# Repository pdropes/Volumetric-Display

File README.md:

# Volumetric-Display, with ESP32 and LED matrix

VOXEL by #dropes

Video: https://youtu.be/vmjfssugH9E

## VOXEL - HARDWARE

- The motor I used the head of a VCR, after opening it, I placed the power transmitter coils inside, the ferrites had to be filed (very carefully) to fit well and then glued them.
- The distance between the coils is very important and must be calibrated in advance, with the help of a power supply with adjustable maximum current. In the receiver, you must connect a low value resistance 2ohms, or a 20W 12V lamp, with a multimeter to monitor the current passing through it.
- Then the emitter must be supplied with 12V, without progressive increases, the supply must be immediate or it will burn out, maximum current of 2A to start.
- The objective is to have the maximum current measured in the receiver, but without saturating the coils, to do this the distance between the coils is slowly reduced, the current rises to a point, then starts to fall, the distance from the coil must be recorded highest measured current.
- It is likely that the source used in these tests will present a current peak when calibrating the distances. You must be very careful not to overheat both the transmitter and the receiver, and you must immediately move the coils away.
- Both must have a heat sink, both on the two boards and on the emitter power transistors.
- The power supply must be at least 50W, with a voltage of 18V to 24V, with a lower voltage the wireless power transmitter will overheat, requiring more current to compensate.
- The IR transmitter and receiver are inside the head through two holes, this head must rotate without touching anything.
- Assembling all the components requires some skills, if you are not able to solder with an oven or heating plate and hot air station, I recommend ordering the PCBs with the components already soldered, joining the two plates will have to be done later.
- The most difficult are the 1024 “0603 LEDs” and the 64 “controller ICs”.
- The PCBs must have the minimum thickness possible, with 0.6mm being a good value, with the LED controller ICs touching them. Their color doesn't matter much, in rotation it becomes unnoticeable.

More calibrations:
- The 1st balance is static, with the boards horizontal and without the tube, weights must be placed, so that no differences are noticed when rotating manually, always horizontally.
- The dynamic balance was achieved by placing a piezo on one of the legs of the box, visualizing the signal amplitude on the oscilloscope, then placing washers at certain points, where the displayed amplitude reduces.
- The tube alignment must also be done, looking for eccentricity and having as little oscillation as possible.
  
These processes can be tedious and time-consuming, be patient.

## VOXEL - SOFTWARE

Project carried out in Arduino IDE v2.2.1
The 1st programming must be via USB, the rest can be via Wi-Fi for the convenience of keeping the tube, this is the best option, the Arduino-ota routine must be configured in advance, with the name and password of the network to be connected, this part must always remain in the code.
Although you chose the ESP32S2, another type of ESP32 should work, it uses the internal RAM for animations, and the optional PSRAM, for pre-calculation of heavier animations.
The USB connection is direct, without the need for a separate IC for this.
Programming the ESP32 must be done with the engine stopped, in all cases.

Programming steps:
- Connect the VOXEL board directly via USB to the PC.
- Open Arduino, in BOARDS MANAGER, find and install “esp32 by Espressif”
- In LIBRARIES MANAGER, find and install “Arduino_ESP32_OTA by Arduino”
- In TOOLS-BOARDS-ESP32-ESP32S2 Dev Module, choose the COM where the VOXEL is connected
- Check the board settings with the attached file “Arduino V2.2.1 config.png”.
- In VOXEL.INO change the name and password of the local network 
- Compile and upload to ESP32.
- After that, all programming does not require a USB connection, on the Arduino IDE, the Wi-Fi port must be visible.
- If you always intend to program via Wi-Fi, the Arduino-ota settings in VOXEL.ino must remain.

New Animation:
- When programming more effects, you must create a blank file in the same folder, extension .h
- Open VOXEL.ino
- Include the new file name in “FX”
- Next, the “FXlast” declaration, must be changed to the last effect number.
- void ISR_IR, which is the int. that detects the complete turn via IR, the procedure to be carried out in this new effect must be included (check the examples already written).
- void ARDUINO_ISR_ATTR, this is a timer that is run 100 times per turn, the reference of the new effect must also be included, or copy 3 lines from another, so that it can be clearly displayed.
- Shared.h file shares variables between VOXEL.ino and effect.h, or use static variables to avoid conflicts.

## WARNING !
The use of acrylic tube is NECESSARY in this assembly!
It keeps the boards in place at the top, prevents air friction, and ensures GREATER SAFETY to the touch.
Its absence can cause PHYSICAL OR VISION DAMAGE, the rotation speed corresponds to between 25 and 42 km/h!

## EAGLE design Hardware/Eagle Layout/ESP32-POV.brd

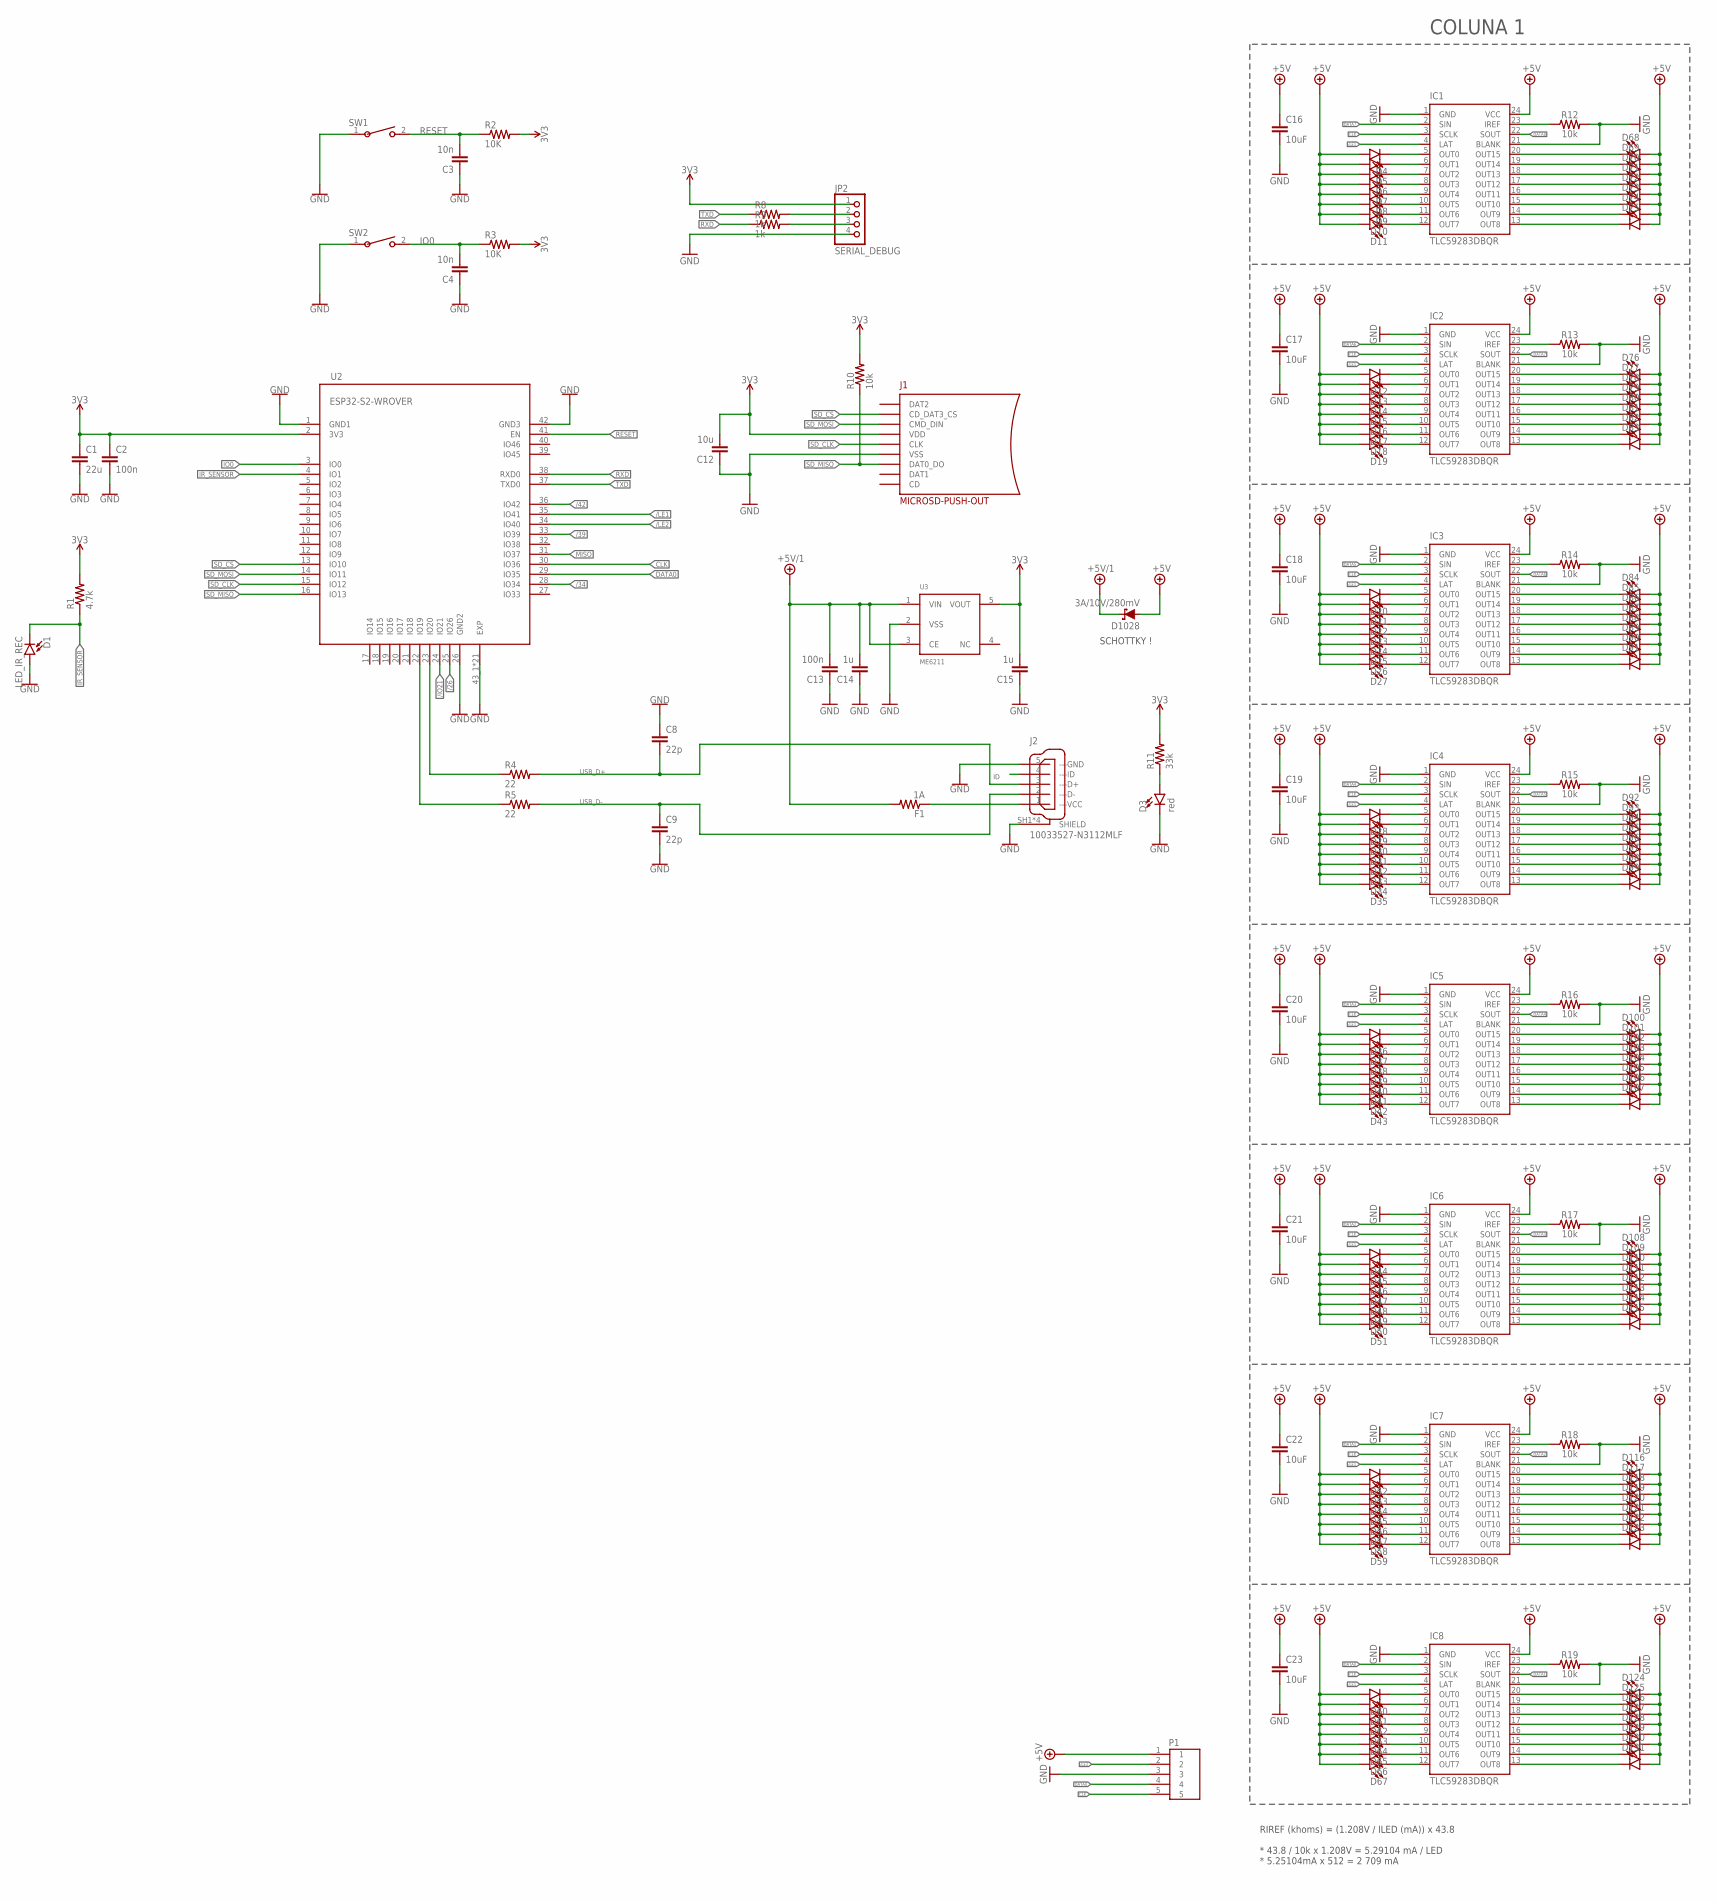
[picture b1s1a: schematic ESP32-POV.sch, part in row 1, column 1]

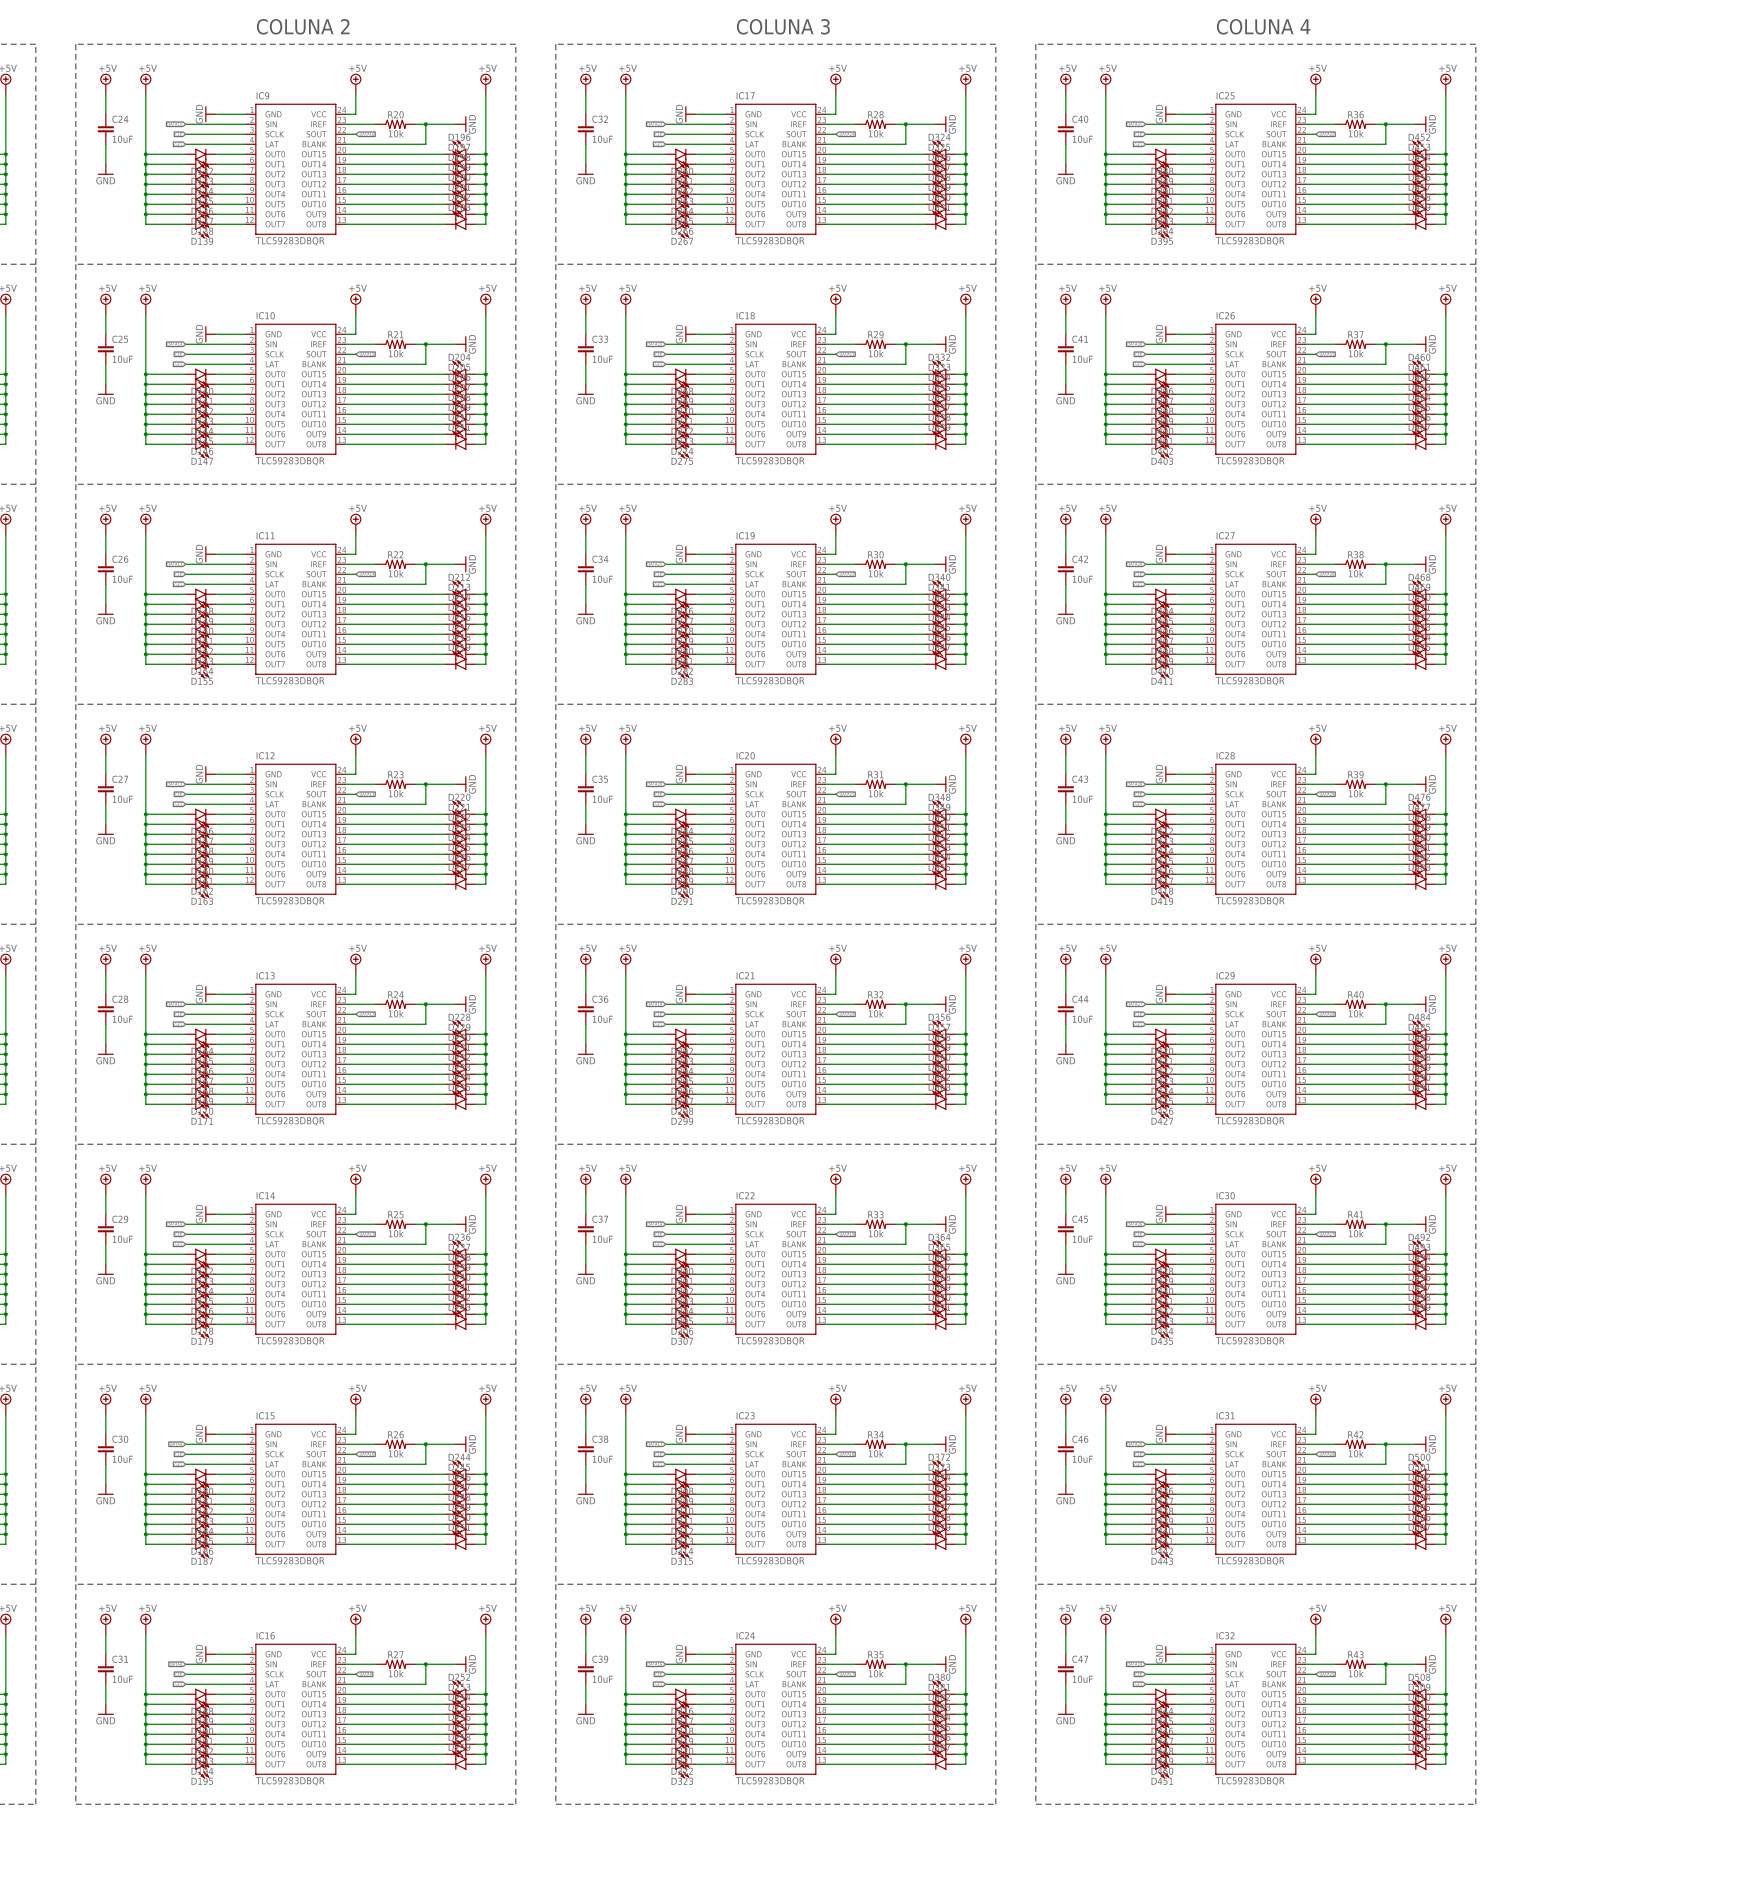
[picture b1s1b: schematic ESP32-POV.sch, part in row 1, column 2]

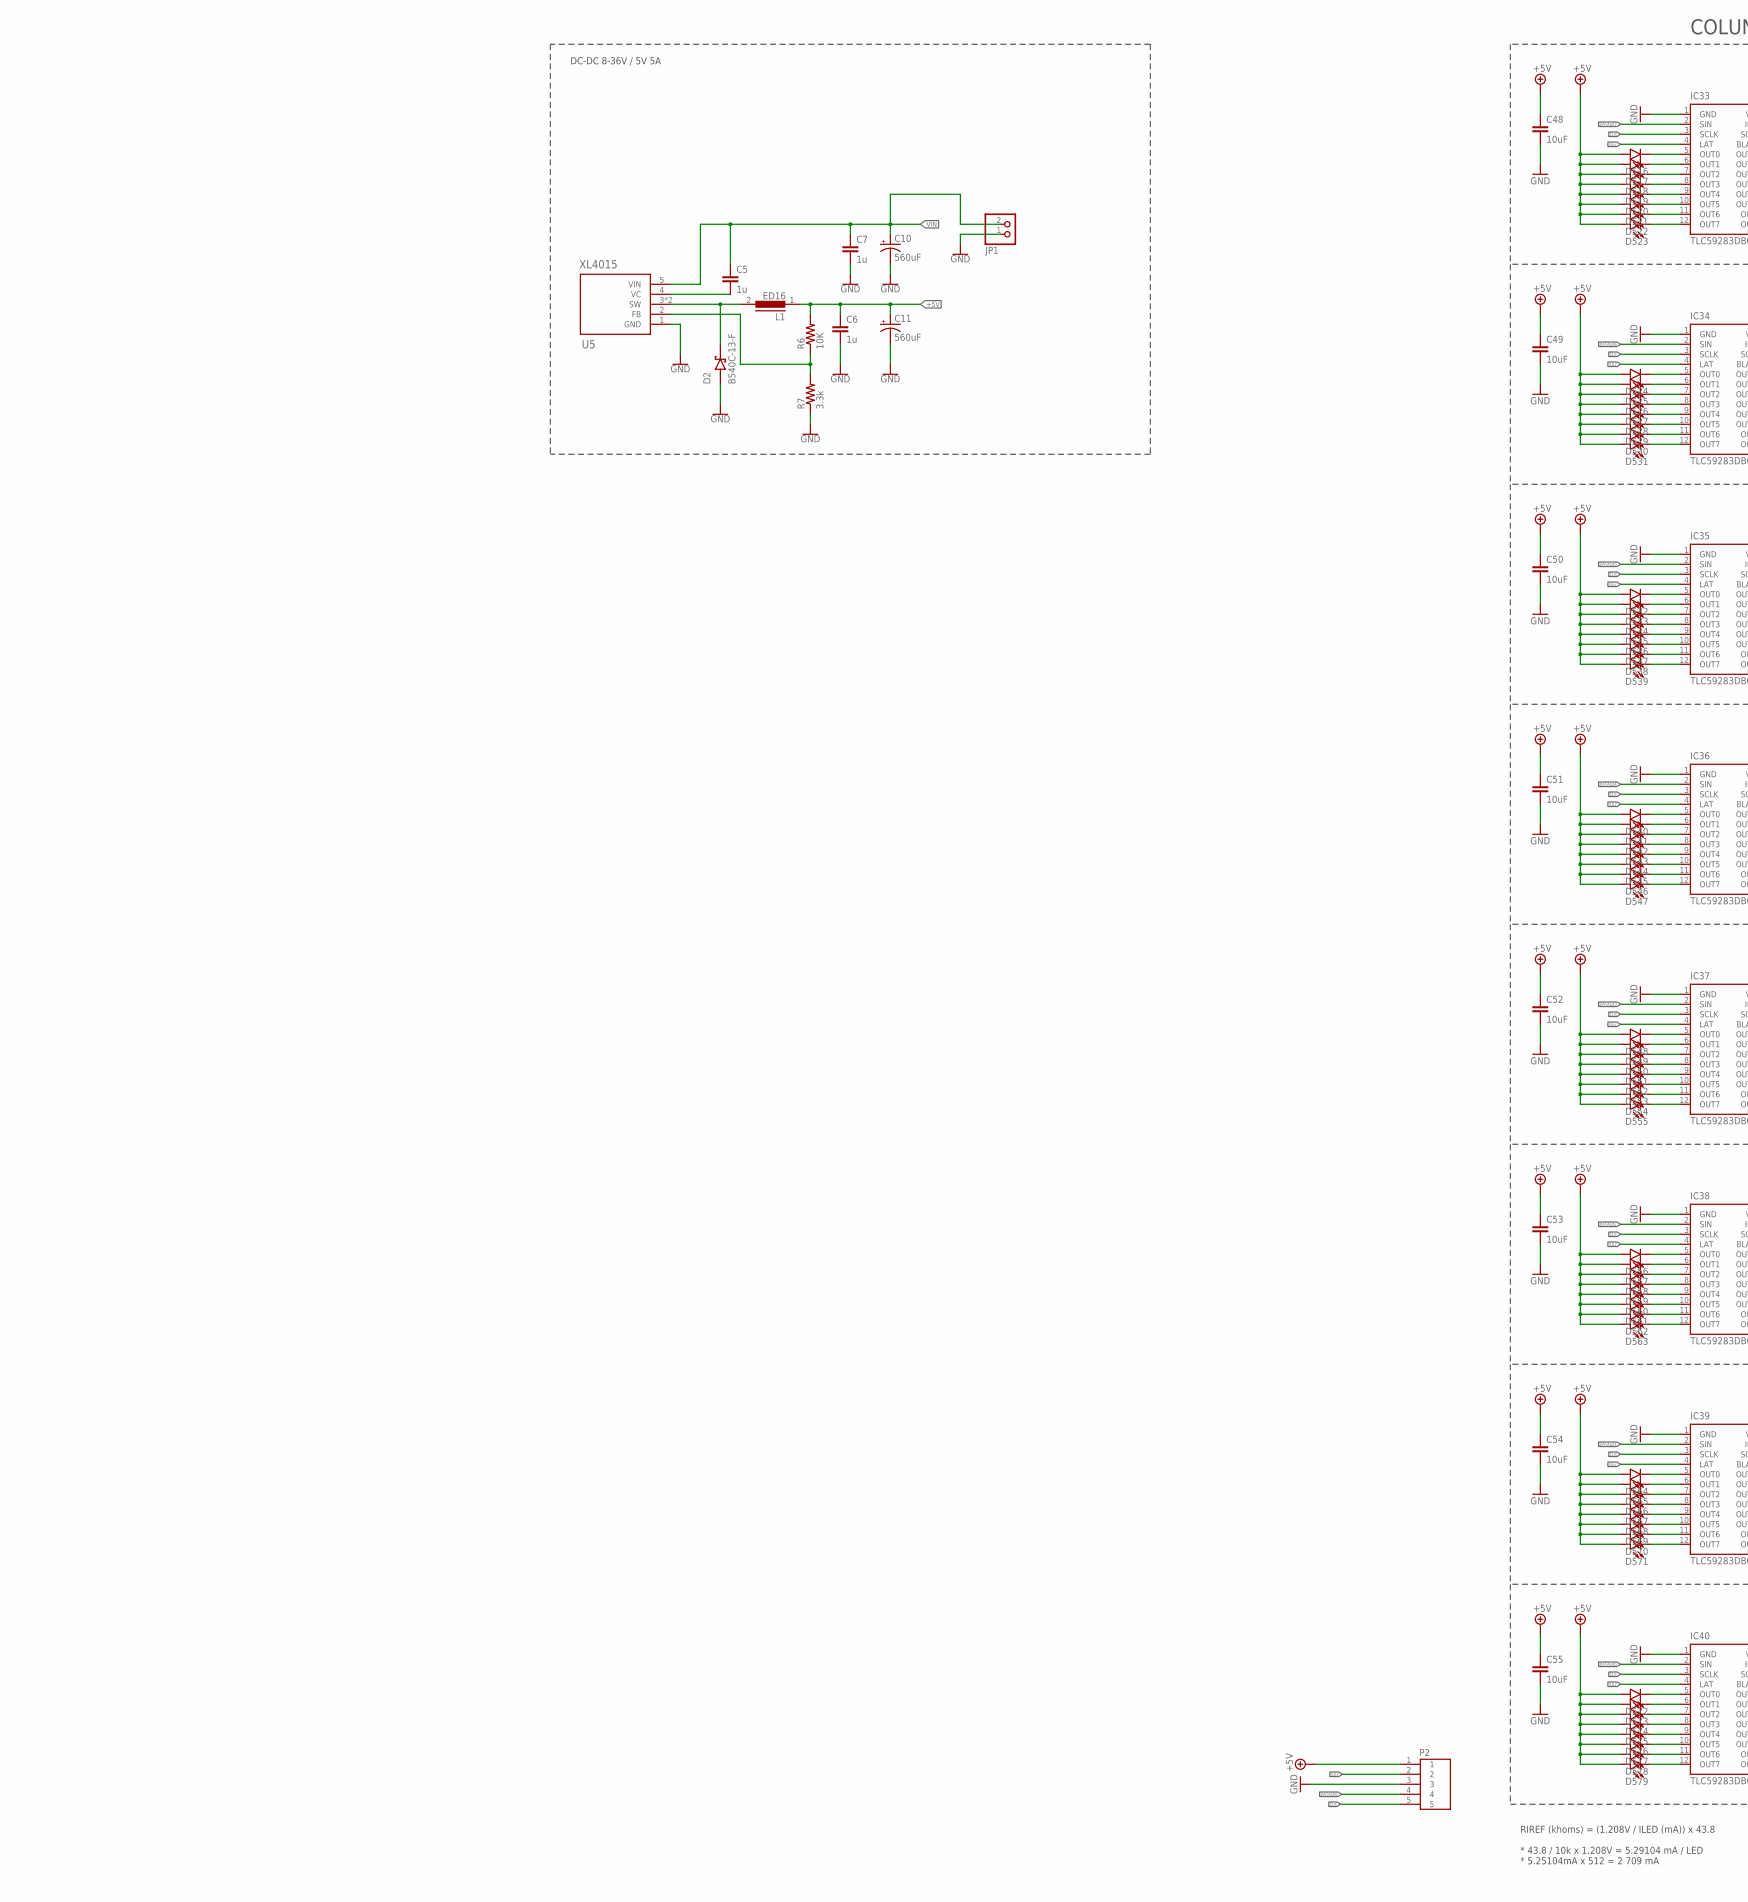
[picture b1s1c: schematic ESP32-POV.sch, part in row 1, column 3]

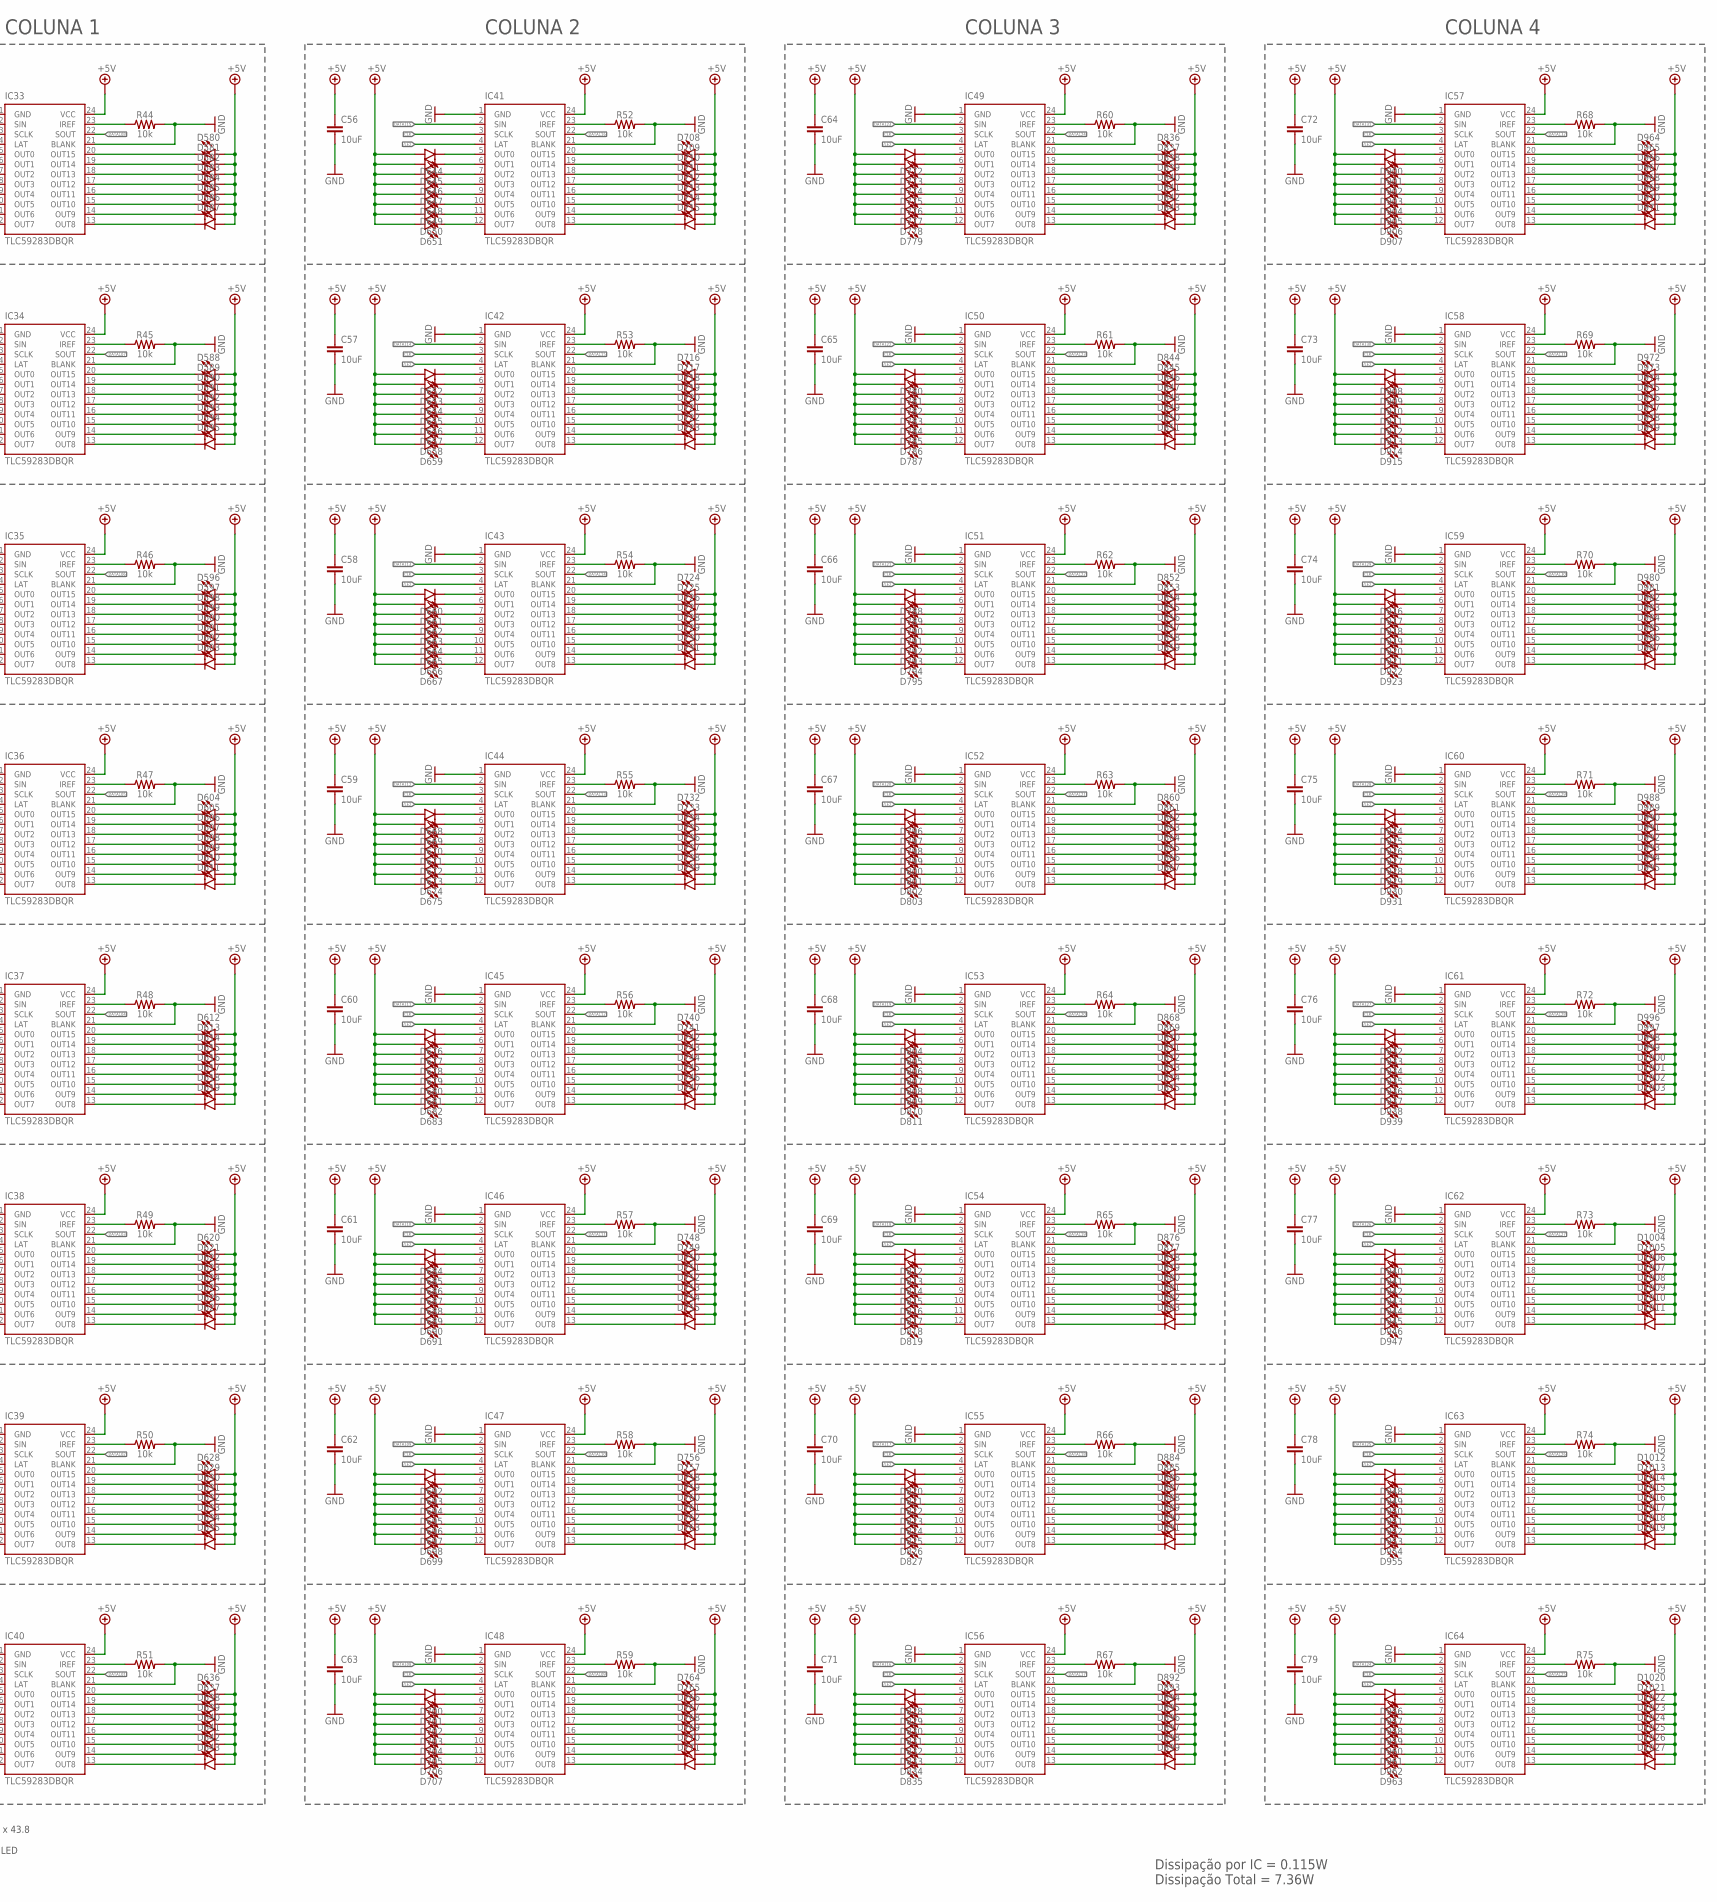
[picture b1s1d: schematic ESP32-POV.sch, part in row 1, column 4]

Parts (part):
C1: 22u; 1206
C2, C13: 100n; 0805
C3, C4: 10n; 0805
C5, C6, C7, C14, C15: 1u; 0805
C8, C9: 22p; 0805
C10, C11: 560uF; PANASONIC_G
C12: 10u; 0805
C16, C17, C18, C19, C20, C21, C22, C23, C24, C25, C26, C27, C28, C29, C30, C31, C32, C33, C34, C35, C36, C37, C38, C39, C40, C41, C42, C43, C44, C45, C46, C47, C48, C49, C50, C51, C52, C53, C54, C55, C56, C57, C58, C59, C60, C61, C62, C63, C64, C65, C66, C67, C68, C69, C70, C71, C72, C73, C74, C75, C76, C77, C78, C79: 10uF; 0603
D1: LED_IR_REC
D2: B540C-13-F; DIOM6959X245N
D3: red; LED-0805
D4, D5, D6, D7, D8, D9, D10, D11, D12, D13, D14, D15, D16, D17, D18, D19, D20, D21, D22, D23, D24, D25, D26, D27, D28, D29, D30, D31, D32, D33, D34, D35, D36, D37, D38, D39, D40, D41, D42, D43, D44, D45, D46, D47, D48, D49, D50, D51, D52, D53, D54, D55, D56, D57, D58, D59, D60, D61, D62, D63, D64, D65, D66, D67, D68, D69, D70, D71, D72, D73, D74, D75, D76, D77, D78, D79, D80, D81, D82, D83, D84, D85, D86, D87, D88, D89, D90, D91, D92, D93, D94, D95, D96, D97, D98, D99, D100, D101, D102, D103, D104, D105, D106, D107, D108, D109, D110, D111, D112, D113, D114, D115, D116, D117, D118, D119, D120, D121, D122, D123, D124, D125, D126, D127, D128, D129, D130, D131, D132, D133, D134, D135, D136, D137, D138, D139, D140, D141, D142, D143, D144, D145, D146, D147, D148, D149, D150, D151, D152, D153, D154, D155, D156, D157, D158, D159, D160, D161, D162, D163, D164, D165, D166, D167, D168, D169, D170, D171, D172, D173, D174, D175, D176, D177, D178, D179, D180, D181, D182, D183, D184, D185, D186, D187, D188, D189, D190, D191, D192, D193, D194, D195, D196, D197, D198, D199, D200, D201, D202, D203, D204, D205, D206, D207, D208, D209, D210, D211, D212, D213, D214, D215, D216, D217, D218, D219, D220, D221, D222, D223, D224, D225, D226, D227, D228, D229, D230, D231, D232, D233, D234, D235, D236, D237, D238, D239, D240, D241, D242, D243, D244, D245, D246, D247, D248, D249, D250, D251, D252, D253, D254, D255, D256, D257, D258, D259, D260, D261, D262, D263, D264, D265, D266, D267, D268, D269, D270, D271, D272, D273, D274, D275, D276, D277, D278, D279, D280, D281, D282, D283, D284, D285, D286, D287, D288, D289, D290, D291, D292, D293, D294, D295, D296, D297, D298, D299, D300, D301, D302, D303, D304, D305, D306, D307, D308, D309, D310, D311, D312, D313, D314, D315, D316, D317, D318, D319, D320, D321, D322, D323, D324, D325, D326, D327, D328, D329, D330, D331, D332, D333, D334, D335, D336, D337, D338, D339, D340, D341, D342, D343, D344, D345, D346, D347, D348, D349, D350, D351, D352, D353, D354, D355, D356, D357, D358, D359, D360, D361, D362, D363, D364, D365, D366, D367, D368, D369, D370, D371, D372, D373, D374, D375, D376, D377, D378, D379, D380, D381, D382, D383, D384, D385, D386, D387, D388, D389, D390, D391, D392, D393, D394, D395, D396, D397, D398, D399, D400, D401, D402, D403, D404, D405, D406, D407, D408, D409, D410, D411, D412, D413, D414, D415, D416, D417, D418, D419, D420, D421, D422, D423, D424, D425, D426, D427, D428, D429, D430, D431, D432, D433, D434, D435, D436, D437, D438, D439, D440, D441, D442, D443, D444, D445, D446, D447, D448, D449, D450, D451, D452, D453, D454, D455, D456, D457, D458, D459, D460, D461, D462, D463, D464, D465, D466, D467, D468, D469, D470, D471, D472, D473, D474, D475, D476, D477, D478, D479, D480, D481, D482, D483, D484, D485, D486, D487, D488, D489, D490, D491, D492, D493, D494, D495, D496, D497, D498, D499, D500, D501, D502, D503, D504, D505, D506, D507, D508, D509, D510, D511, D512, D513, D514, D515, D516, D517, D518, D519, D520, D521, D522, D523, D524, D525, D526, D527, D528, D529, D530, D531, D532, D533, D534, D535, D536, D537, D538, D539, D540, D541, D542, D543, D544, D545, D546, D547, D548, D549, D550, D551, D552, D553, D554, D555, D556, D557, D558, D559, D560, D561, D562, D563, D564, D565, D566, D567, D568, D569, D570, D571, D572, D573, D574, D575, D576, D577, D578, D579, D580, D581, D582, D583, D584, D585, D586, D587, D588, D589, D590, D591, D592, D593, D594, D595, D596, D597, D598, D599, D600, D601, D602, D603, D604, D605, D606, D607, D608, D609, D610, D611, D612, D613, D614, D615, D616, D617, D618, D619, D620, D621, D622, D623, D624, D625, D626, D627, D628, D629, D630, D631, D632, D633, D634, D635, D636, D637, D638, D639, D640, D641, D642, D643, D644, D645, D646, D647, D648, D649, D650, D651, D652, D653, D654, D655, D656, D657, D658, D659, D660, D661, D662, D663, D664, D665, D666, D667, D668, D669, D670, D671, D672, D673, D674, D675, D676, D677, D678, D679, D680, D681, D682, D683, D684, D685, D686, D687, D688, D689, D690, D691, D692, D693, D694, D695, D696, D697, D698, D699, D700, D701, D702, D703, D704, D705, D706, D707, D708, D709, D710, D711, D712, D713, D714, D715, D716, D717, D718, D719, D720, D721, D722, D723, D724, D725, D726, D727, D728, D729, D730, D731, D732, D733, D734, D735, D736, D737, D738, D739, D740, D741, D742, D743, D744, D745, D746, D747, D748, D749, D750, D751, D752, D753, D754, D755, D756, D757, D758, D759, D760, D761, D762, D763, D764, D765, D766, D767, D768, D769, D770, D771, D772, D773, D774, D775, D776, D777, D778, D779, D780, D781, D782, D783, D784, D785, D786, D787, D788, D789, D790, D791, D792, D793, D794, D795, D796, D797, D798, D799, D800, D801, D802, D803, D804, D805, D806, D807, D808, D809, D810, D811, D812, D813, D814, D815, D816, D817, D818, D819, D820, D821, D822, D823, D824, D825, D826, D827, D828, D829, D830, D831, D832, D833, D834, D835, D836, D837, D838, D839, D840, D841, D842, D843, D844, D845, D846, D847, D848, D849, D850, D851, D852, D853, D854, D855, D856, D857, D858, D859, D860, D861, D862, D863, D864, D865, D866, D867, D868, D869, D870, D871, D872, D873, D874, D875, D876, D877, D878, D879, D880, D881, D882, D883, D884, D885, D886, D887, D888, D889, D890, D891, D892, D893, D894, D895, D896, D897, D898, D899, D900, D901, D902, D903, D904, D905, D906, D907, D908, D909, D910, D911, D912, D913, D914, D915, D916, D917, D918, D919, D920, D921, D922, D923, D924, D925, D926, D927, D928, D929, D930, D931, D932, D933, D934, D935, D936, D937, D938, D939, D940, D941, D942, D943, D944, D945, D946, D947, D948, D949, D950, D951, D952, D953, D954, D955, D956, D957, D958, D959, D960, D961, D962, D963, D964, D965, D966, D967, D968, D969, D970, D971, D972, D973, D974, D975, D976, D977, D978, D979, D980, D981, D982, D983, D984, D985, D986, D987, D988, D989, D990, D991, D992, D993, D994, D995, D996, D997, D998, D999, D1000, D1001, D1002, D1003, D1004, D1005, D1006, D1007, D1008, D1009, D1010, D1011, D1012, D1013, D1014, D1015, D1016, D1017, D1018, D1019, D1020, D1021, D1022, D1023, D1024, D1025, D1026, D1027: LED-BLUE0603; LED-0603
D1028: 3A/10V/280mV; SOD-323
F1: 1A; 0805
IC1, IC2, IC3, IC4, IC5, IC6, IC7, IC8, IC9, IC10, IC11, IC12, IC13, IC14, IC15, IC16, IC17, IC18, IC19, IC20, IC21, IC22, IC23, IC24, IC25, IC26, IC27, IC28, IC29, IC30, IC31, IC32, IC33, IC34, IC35, IC36, IC37, IC38, IC39, IC40, IC41, IC42, IC43, IC44, IC45, IC46, IC47, IC48, IC49, IC50, IC51, IC52, IC53, IC54, IC55, IC56, IC57, IC58, IC59, IC60, IC61, IC62, IC63, IC64: TLC59283DBQR; DBQ24_TEX
J1: MICROSD-PUSH-OUT
J2: 10033527-N3112MLF; AMPHENOL_10033527-N3112MLF
JP1: PINHD-1X2; 1X02
JP2: SERIAL_DEBUG; PINHEAD_1X04
L1: ED16
P1, P2: HEADER5
R1: 4.7k; 0805
R2, R3, R6: 10K; 0805
R4, R5: 22; 0805
R7: 3.3k; 0805
R8, R9: 1k; 0805
R10: 10k; 0805
R11: 33k; 0805
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
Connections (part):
+5V: C6.1, C11.+, C16.1, C17.1, C18.1, C19.1, C20.1, C21.1, C22.1, C23.1, C24.1, C25.1, C26.1, C27.1, C28.1, C29.1, C30.1, C31.1, C32.1, C33.1, C34.1, C35.1, C36.1, C37.1, C38.1, C39.1, C40.1, C41.1, C42.1, C43.1, C44.1, C45.1, C46.1, C47.1, C48.1, C49.1, C50.1, C51.1, C52.1, C53.1, C54.1, C55.1, C56.1, C57.1, C58.1, C59.1, C60.1, C61.1, C62.1, C63.1, C64.1, C65.1, C66.1, C67.1, C68.1, C69.1, C70.1, C71.1, C72.1, C73.1, C74.1, C75.1, C76.1, C77.1, C78.1, C79.1, D4.A, D5.A, D6.A, D7.A, D8.A, D9.A, D10.A, D11.A, D12.A, D13.A, D14.A, D15.A, D16.A, D17.A, D18.A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
+5V/1: C13.2, C14.2, D1028.C, F1.2, U3.1 (VIN), U3.3 (CE)
/26: U2.25 (IO26)
/34: U2.28 (IO34)
/39: U2.33 (IO39)
/42: U2.36 (IO42)
/IO21: U2.24 (IO21)
/LE1: IC1.4 (LAT), IC2.4 (LAT), IC3.4 (LAT), IC4.4 (LAT), IC5.4 (LAT), IC6.4 (LAT), IC7.4 (LAT), IC8.4 (LAT), IC9.4 (LAT), IC10.4 (LAT), IC11.4 (LAT), IC12.4 (LAT), IC13.4 (LAT), IC14.4 (LAT), IC15.4 (LAT), IC16.4 (LAT), IC17.4 (LAT), IC18.4 (LAT), IC19.4 (LAT), IC20.4 (LAT), IC21.4 (LAT), IC22.4 (LAT), IC23.4 (LAT), IC24.4 (LAT), IC25.4 (LAT), IC26.4 (LAT), IC27.4 (LAT), IC28.4 (LAT), IC29.4 (LAT), IC30.4 (LAT), IC31.4 (LAT), IC32.4 (LAT), U2.35 (IO41)
/LE2: IC33.4 (LAT), IC34.4 (LAT), IC35.4 (LAT), IC36.4 (LAT), IC37.4 (LAT), IC38.4 (LAT), IC39.4 (LAT), IC40.4 (LAT), IC41.4 (LAT), IC42.4 (LAT), IC43.4 (LAT), IC44.4 (LAT), IC45.4 (LAT), IC46.4 (LAT), IC47.4 (LAT), IC48.4 (LAT), IC49.4 (LAT), IC50.4 (LAT), IC51.4 (LAT), IC52.4 (LAT), IC53.4 (LAT), IC54.4 (LAT), IC55.4 (LAT), IC56.4 (LAT), IC57.4 (LAT), IC58.4 (LAT), IC59.4 (LAT), IC60.4 (LAT), IC61.4 (LAT), IC62.4 (LAT), IC63.4 (LAT), IC64.4 (LAT), P1.2, P2.2, U2.34 (IO40)
CLK: IC1.3 (SCLK), IC2.3 (SCLK), IC3.3 (SCLK), IC4.3 (SCLK), IC5.3 (SCLK), IC6.3 (SCLK), IC7.3 (SCLK), IC8.3 (SCLK), IC9.3 (SCLK), IC10.3 (SCLK), IC11.3 (SCLK), IC12.3 (SCLK), IC13.3 (SCLK), IC14.3 (SCLK), IC15.3 (SCLK), IC16.3 (SCLK), IC17.3 (SCLK), IC18.3 (SCLK), IC19.3 (SCLK), IC20.3 (SCLK), IC21.3 (SCLK), IC22.3 (SCLK), IC23.3 (SCLK), IC24.3 (SCLK), IC25.3 (SCLK), IC26.3 (SCLK), IC27.3 (SCLK), IC28.3 (SCLK), IC29.3 (SCLK), IC30.3 (SCLK), IC31.3 (SCLK), IC32.3 (SCLK), IC33.3 (SCLK), IC34.3 (SCLK), IC35.3 (SCLK), IC36.3 (SCLK), IC37.3 (SCLK), IC38.3 (SCLK), IC39.3 (SCLK), IC40.3 (SCLK), IC41.3 (SCLK), IC42.3 (SCLK), IC43.3 (SCLK), IC44.3 (SCLK), IC45.3 (SCLK), IC46.3 (SCLK), IC47.3 (SCLK), IC48.3 (SCLK), IC49.3 (SCLK), IC50.3 (SCLK), IC51.3 (SCLK), IC52.3 (SCLK), IC53.3 (SCLK), IC54.3 (SCLK), IC55.3 (SCLK), IC56.3 (SCLK), IC57.3 (SCLK), IC58.3 (SCLK), IC59.3 (SCLK), IC60.3 (SCLK), IC61.3 (SCLK), IC62.3 (SCLK), IC63.3 (SCLK), IC64.3 (SCLK), P1.5, P2.5, U2.30 (IO36)
DATA0: IC8.2 (SIN), P1.4, U2.29 (IO35)
DATA1: IC7.2 (SIN), IC8.22 (SOUT)
DATA2: IC6.2 (SIN), IC7.22 (SOUT)
DATA3: IC5.2 (SIN), IC6.22 (SOUT)
DATA4: IC4.2 (SIN), IC5.22 (SOUT)
DATA5: IC3.2 (SIN), IC4.22 (SOUT)
DATA6: IC2.2 (SIN), IC3.22 (SOUT)
DATA7: IC1.2 (SIN), IC2.22 (SOUT)
DATA8: IC1.22 (SOUT), IC16.2 (SIN)
DATA9: IC15.2 (SIN), IC16.22 (SOUT)
DATA10: IC14.2 (SIN), IC15.22 (SOUT)
DATA11: IC13.2 (SIN), IC14.22 (SOUT)
DATA12: IC12.2 (SIN), IC13.22 (SOUT)
DATA13: IC11.2 (SIN), IC12.22 (SOUT)
DATA14: IC10.2 (SIN), IC11.22 (SOUT)
DATA15: IC9.2 (SIN), IC10.22 (SOUT)
DATA16: IC9.22 (SOUT), IC24.2 (SIN)
DATA17: IC23.2 (SIN), IC24.22 (SOUT)
DATA18: IC22.2 (SIN), IC23.22 (SOUT)
DATA19: IC21.2 (SIN), IC22.22 (SOUT)
DATA20: IC20.2 (SIN), IC21.22 (SOUT)
DATA21: IC19.2 (SIN), IC20.22 (SOUT)
DATA22: IC18.2 (SIN), IC19.22 (SOUT)
DATA23: IC17.2 (SIN), IC18.22 (SOUT)
DATA24: IC17.22 (SOUT), IC32.2 (SIN)
DATA25: IC31.2 (SIN), IC32.22 (SOUT)
DATA26: IC30.2 (SIN), IC31.22 (SOUT)
DATA27: IC29.2 (SIN), IC30.22 (SOUT)
DATA28: IC28.2 (SIN), IC29.22 (SOUT)
DATA29: IC27.2 (SIN), IC28.22 (SOUT)
DATA30: IC26.2 (SIN), IC27.22 (SOUT)
DATA31: IC25.2 (SIN), IC26.22 (SOUT)
DATA32: IC25.22 (SOUT)
DATA100: IC40.2 (SIN), P2.4
DATA101: IC39.2 (SIN), IC40.22 (SOUT)
DATA102: IC38.2 (SIN), IC39.22 (SOUT)
DATA103: IC37.2 (SIN), IC38.22 (SOUT)
DATA104: IC36.2 (SIN), IC37.22 (SOUT)
DATA105: IC35.2 (SIN), IC36.22 (SOUT)
DATA106: IC34.2 (SIN), IC35.22 (SOUT)
DATA107: IC33.2 (SIN), IC34.22 (SOUT)
DATA108: IC33.22 (SOUT), IC48.2 (SIN)
DATA109: IC47.2 (SIN), IC48.22 (SOUT)
DATA110: IC46.2 (SIN), IC47.22 (SOUT)
DATA111: IC45.2 (SIN), IC46.22 (SOUT)
DATA112: IC44.2 (SIN), IC45.22 (SOUT)
DATA113: IC43.2 (SIN), IC44.22 (SOUT)
DATA114: IC42.2 (SIN), IC43.22 (SOUT)
DATA115: IC41.2 (SIN), IC42.22 (SOUT)
DATA116: IC41.22 (SOUT), IC56.2 (SIN)
DATA117: IC55.2 (SIN), IC56.22 (SOUT)
DATA118: IC54.2 (SIN), IC55.22 (SOUT)
DATA119: IC53.2 (SIN), IC54.22 (SOUT)
DATA120: IC52.2 (SIN), IC53.22 (SOUT)
DATA121: IC51.2 (SIN), IC52.22 (SOUT)
DATA122: IC50.2 (SIN), IC51.22 (SOUT)
DATA123: IC49.2 (SIN), IC50.22 (SOUT)
DATA124: IC49.22 (SOUT), IC64.2 (SIN)
DATA125: IC63.2 (SIN), IC64.22 (SOUT)
DATA126: IC62.2 (SIN), IC63.22 (SOUT)
DATA127: IC61.2 (SIN), IC62.22 (SOUT)
DATA128: IC60.2 (SIN), IC61.22 (SOUT)
DATA129: IC59.2 (SIN), IC60.22 (SOUT)
DATA130: IC58.2 (SIN), IC59.22 (SOUT)
DATA131: IC57.2 (SIN), IC58.22 (SOUT)
DATA132: IC57.22 (SOUT)
GND: C1.2, C2.2, C3.1, C4.1, C6.2, C7.2, C8.1, C9.2, C10.-, C11.-, C12.1, C13.1, C14.1, C15.1, C16.2, C17.2, C18.2, C19.2, C20.2, C21.2, C22.2, C23.2, C24.2, C25.2, C26.2, C27.2, C28.2, C29.2, C30.2, C31.2, C32.2, C33.2, C34.2, C35.2, C36.2, C37.2, C38.2, C39.2, C40.2, C41.2, C42.2, C43.2, C44.2, C45.2, C46.2, C47.2, C48.2, C49.2, C50.2, C51.2, C52.2, C53.2, C54.2, C55.2, C56.2, C57.2, C58.2, C59.2, C60.2, C61.2, C62.2, C63.2, C64.2, C65.2, C66.2, C67.2, C68.2, C69.2, C70.2, C71.2, C72.2, C73.2, C74.2, C75.2, C76.2, C77.2, C78.2, C79.2, D1.A, D2.A, D3.C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
ID: J2.4 (---ID)
IO0: C4.2, R3.1, SW2.2, U2.3 (IO0)
IO52: R4.1, U2.23 (IO20)
IO53: R5.1, U2.22 (IO19)
IR_SENSOR: D1.K (C), R1.1, U2.4 (IO1)
MISO: U2.31 (IO37)
unnamed: D52.C, IC7.5 (OUT0)
unnamed: D53.C, IC7.6 (OUT1)
unnamed: D54.C, IC7.7 (OUT2)
unnamed: D55.C, IC7.8 (OUT3)
unnamed: D56.C, IC7.9 (OUT4)
unnamed: D58.C, IC7.11 (OUT6)
unnamed: D59.C, IC7.12 (OUT7)
unnamed: D123.C, IC7.13 (OUT8)
unnamed: D122.C, IC7.14 (OUT9)
unnamed: D121.C, IC7.15 (OUT10)
unnamed: D120.C, IC7.16 (OUT11)
unnamed: D119.C, IC7.17 (OUT12)
unnamed: D118.C, IC7.18 (OUT13)
unnamed: D117.C, IC7.19 (OUT14)
unnamed: D116.C, IC7.20 (OUT15)
unnamed: D57.C, IC7.10 (OUT5)
unnamed: IC7.23 (IREF), R18.1
unnamed: D44.C, IC6.5 (OUT0)
unnamed: D45.C, IC6.6 (OUT1)
unnamed: D46.C, IC6.7 (OUT2)
unnamed: D47.C, IC6.8 (OUT3)
unnamed: D48.C, IC6.9 (OUT4)
unnamed: D50.C, IC6.11 (OUT6)
unnamed: D51.C, IC6.12 (OUT7)
unnamed: D115.C, IC6.13 (OUT8)
unnamed: D114.C, IC6.14 (OUT9)
unnamed: D113.C, IC6.15 (OUT10)
unnamed: D112.C, IC6.16 (OUT11)
unnamed: D111.C, IC6.17 (OUT12)
unnamed: D110.C, IC6.18 (OUT13)
unnamed: D109.C, IC6.19 (OUT14)
unnamed: D108.C, IC6.20 (OUT15)
unnamed: D49.C, IC6.10 (OUT5)
unnamed: IC6.23 (IREF), R17.1
unnamed: D572.C, IC40.5 (OUT0)
unnamed: D36.C, IC5.5 (OUT0)
unnamed: D37.C, IC5.6 (OUT1)
unnamed: D38.C, IC5.7 (OUT2)
unnamed: D39.C, IC5.8 (OUT3)
unnamed: D40.C, IC5.9 (OUT4)
unnamed: D42.C, IC5.11 (OUT6)
unnamed: D43.C, IC5.12 (OUT7)
unnamed: D107.C, IC5.13 (OUT8)
unnamed: D106.C, IC5.14 (OUT9)
unnamed: D105.C, IC5.15 (OUT10)
unnamed: D104.C, IC5.16 (OUT11)
unnamed: D103.C, IC5.17 (OUT12)
unnamed: D102.C, IC5.18 (OUT13)
unnamed: D101.C, IC5.19 (OUT14)
unnamed: D100.C, IC5.20 (OUT15)
unnamed: D41.C, IC5.10 (OUT5)
unnamed: IC5.23 (IREF), R16.1
unnamed: D28.C, IC4.5 (OUT0)
unnamed: D29.C, IC4.6 (OUT1)
unnamed: D30.C, IC4.7 (OUT2)
unnamed: D31.C, IC4.8 (OUT3)
unnamed: D32.C, IC4.9 (OUT4)
unnamed: D34.C, IC4.11 (OUT6)
unnamed: D35.C, IC4.12 (OUT7)
unnamed: D99.C, IC4.13 (OUT8)
unnamed: D98.C, IC4.14 (OUT9)
unnamed: D97.C, IC4.15 (OUT10)
unnamed: D96.C, IC4.16 (OUT11)
unnamed: D95.C, IC4.17 (OUT12)
unnamed: D94.C, IC4.18 (OUT13)
unnamed: D93.C, IC4.19 (OUT14)
unnamed: D92.C, IC4.20 (OUT15)
unnamed: D33.C, IC4.10 (OUT5)
unnamed: IC4.23 (IREF), R15.1
unnamed: D20.C, IC3.5 (OUT0)
unnamed: D21.C, IC3.6 (OUT1)
unnamed: D22.C, IC3.7 (OUT2)
unnamed: D23.C, IC3.8 (OUT3)
unnamed: D24.C, IC3.9 (OUT4)
unnamed: D26.C, IC3.11 (OUT6)
unnamed: D27.C, IC3.12 (OUT7)
unnamed: D91.C, IC3.13 (OUT8)
unnamed: D90.C, IC3.14 (OUT9)
unnamed: D89.C, IC3.15 (OUT10)
unnamed: D88.C, IC3.16 (OUT11)
unnamed: D87.C, IC3.17 (OUT12)
unnamed: D86.C, IC3.18 (OUT13)
unnamed: D85.C, IC3.19 (OUT14)
unnamed: D84.C, IC3.20 (OUT15)
unnamed: D25.C, IC3.10 (OUT5)
unnamed: IC3.23 (IREF), R14.1
unnamed: D60.C, IC8.5 (OUT0)
unnamed: D61.C, IC8.6 (OUT1)
unnamed: D62.C, IC8.7 (OUT2)
unnamed: D63.C, IC8.8 (OUT3)
unnamed: D64.C, IC8.9 (OUT4)
unnamed: D66.C, IC8.11 (OUT6)
unnamed: D67.C, IC8.12 (OUT7)
unnamed: D131.C, IC8.13 (OUT8)
unnamed: D130.C, IC8.14 (OUT9)
unnamed: D129.C, IC8.15 (OUT10)
unnamed: D128.C, IC8.16 (OUT11)
unnamed: D127.C, IC8.17 (OUT12)
unnamed: D126.C, IC8.18 (OUT13)
unnamed: D125.C, IC8.19 (OUT14)
unnamed: D124.C, IC8.20 (OUT15)
unnamed: D65.C, IC8.10 (OUT5)
unnamed: IC8.23 (IREF), R19.1
unnamed: D12.C, IC2.5 (OUT0)
unnamed: D13.C, IC2.6 (OUT1)
unnamed: D14.C, IC2.7 (OUT2)
unnamed: D15.C, IC2.8 (OUT3)
unnamed: D16.C, IC2.9 (OUT4)
unnamed: D18.C, IC2.11 (OUT6)
unnamed: D19.C, IC2.12 (OUT7)
unnamed: D83.C, IC2.13 (OUT8)
unnamed: D82.C, IC2.14 (OUT9)
unnamed: D81.C, IC2.15 (OUT10)
unnamed: D80.C, IC2.16 (OUT11)
unnamed: D79.C, IC2.17 (OUT12)
unnamed: D78.C, IC2.18 (OUT13)
unnamed: D77.C, IC2.19 (OUT14)
unnamed: D76.C, IC2.20 (OUT15)
unnamed: D17.C, IC2.10 (OUT5)
unnamed: IC2.23 (IREF), R13.1
unnamed: D4.C, IC1.5 (OUT0)
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
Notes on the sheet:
COLUNA 1
COLUNA 2
COLUNA 3
COLUNA 4
RIREF (khoms) = (1.208V / ILED (mA)) x 43.8 * 43.8 / 10k x 1.208V = 5.29104 mA / LED * 5.25104mA x 512 = 2 709 mA
DC-DC 8-36V / 5V 5A
Dissipação por IC = 0.115W Dissipação Total = 7.36W
SCHOTTKY !

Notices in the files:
parts and their libraries:
SparkFun-LED: Licensing: Creative Commons ShareAlike 4.0 International - https://creativecommons.org/licenses/by-sa/4.0
SparkFun: Licensing: CC v3.0 Share-Alike You are welcome to use this library for commercial purposes.
COPYRIGHT: Copyright (C) 2024 Ultra Librarian. All rights reserved.
